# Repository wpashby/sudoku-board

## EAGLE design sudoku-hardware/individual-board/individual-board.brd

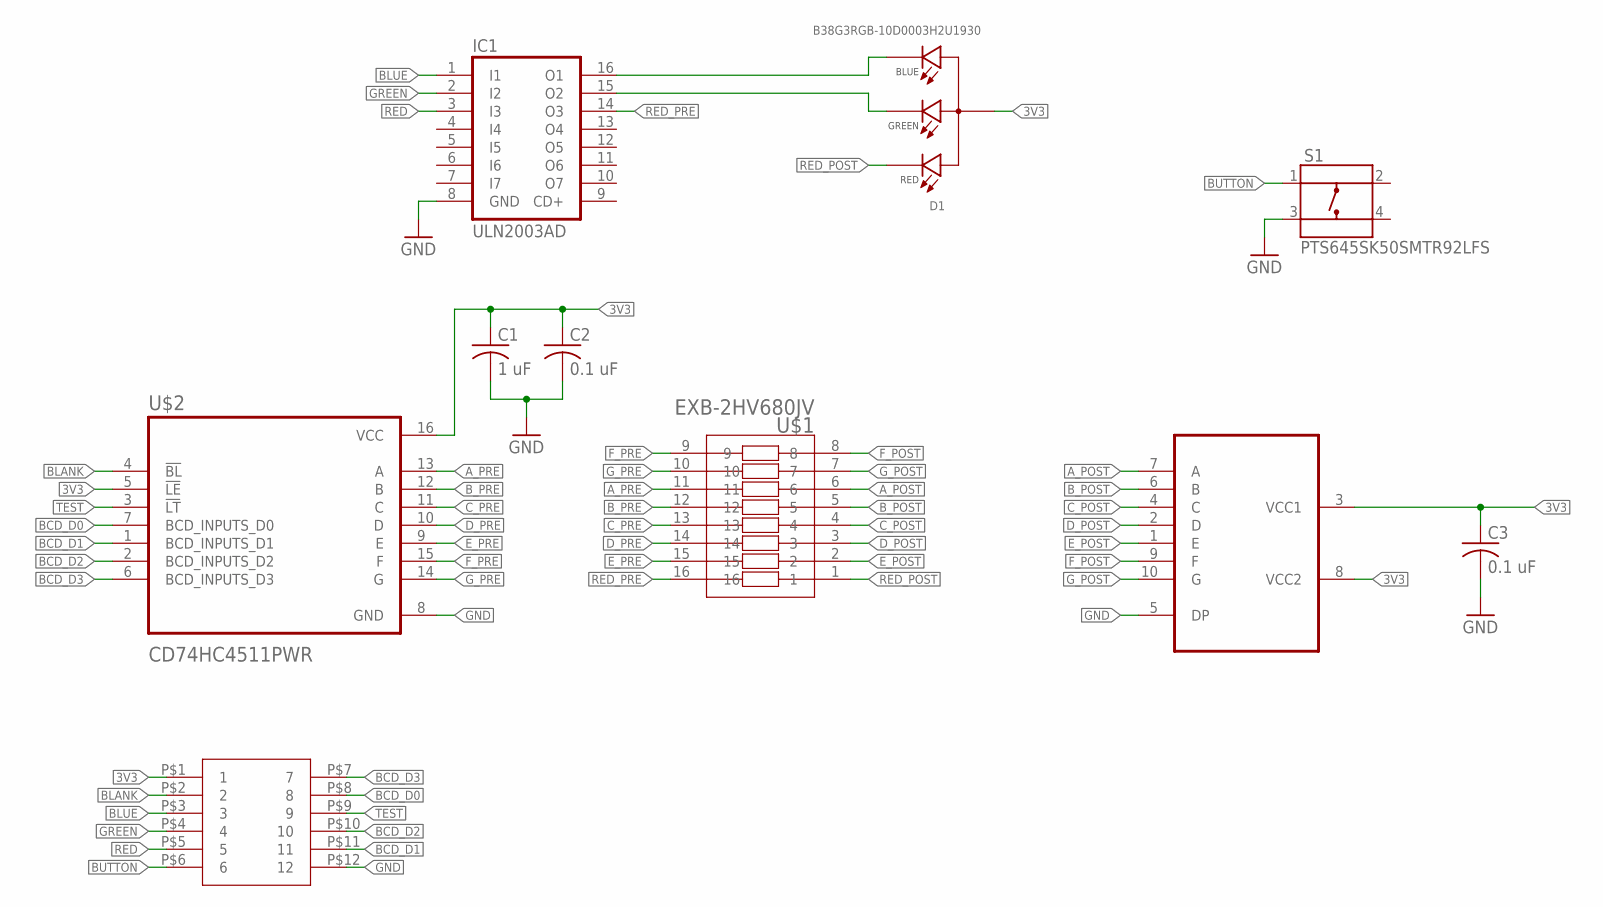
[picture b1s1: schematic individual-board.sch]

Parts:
C1: 1 uF; C0603
C2, C3: 0.1 uF; C0603
D1: B38G3RGB-10D0003H2U1930; LED_B38G3RGB-10D0003H2U1930
IC1: ULN2003AD; SO16
S1: PTS645SK50SMTR92LFS; SW_PTS645SK50SMTR92LFS
U$1: EXB-2HV680JV; 2HV
U$2: CD74HC4511PWR
U$3: INND-SS30RAB
U$4: 2X6-EDGE-CONNECTOR

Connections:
3V3: C1.1, C2.1, C3.1, D1.3 (A), U$2.5 (!LE), U$2.16 (VCC), U$3.3 (VCC1), U$3.8 (VCC2), U$4.P$1 (1)
A_POST: U$1.6, U$3.7 (A)
A_PRE: U$1.11, U$2.13 (A)
BCD_D0: U$2.7 (BCD_INPUTS_D0), U$4.P$8 (8)
BCD_D1: U$2.1 (BCD_INPUTS_D1), U$4.P$11 (11)
BCD_D2: U$2.2 (BCD_INPUTS_D2), U$4.P$10 (10)
BCD_D3: U$2.6 (BCD_INPUTS_D3), U$4.P$7 (7)
BLANK: U$2.4 (!BL), U$4.P$2 (2)
BLUE: IC1.1 (I1), U$4.P$3 (3)
BUTTON: S1.1, U$4.P$6 (6)
B_POST: U$1.5, U$3.6 (B)
B_PRE: U$1.12, U$2.12 (B)
C_POST: U$1.4, U$3.4 (C)
C_PRE: U$1.13, U$2.11 (C)
D_POST: U$1.3, U$3.2 (D)
D_PRE: U$1.14, U$2.10 (D)
E_POST: U$1.2, U$3.1 (E)
E_PRE: U$1.15, U$2.9 (E)
F_POST: U$1.8, U$3.9 (F)
F_PRE: U$1.9, U$2.15 (F)
GND: C1.2, C2.2, C3.2, IC1.8 (GND), S1.3, U$2.8 (GND), U$3.5 (DP), U$4.P$12 (12)
GREEN: IC1.2 (I2), U$4.P$4 (4)
G_POST: U$1.7, U$3.10 (G)
G_PRE: U$1.10, U$2.14 (G)
unnamed: D1.2 (B_C), IC1.16 (O1)
unnamed: D1.1 (G_C), IC1.15 (O2)
RED: IC1.3 (I3), U$4.P$5 (5)
RED_POST: D1.4 (R_C), U$1.1
RED_PRE: IC1.14 (O3), U$1.16
TEST: U$2.3 (!LT), U$4.P$9 (9)

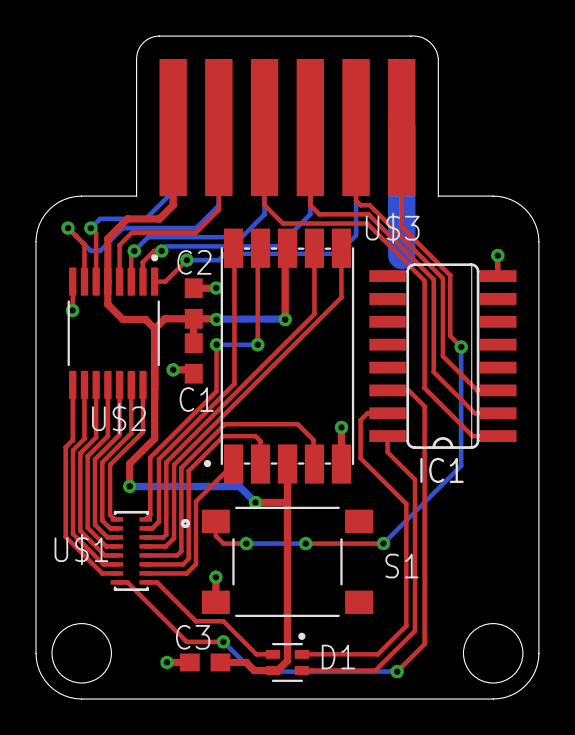
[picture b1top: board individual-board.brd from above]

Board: 2 copper layers, 27.9 x 36.8 mm, 10 parts (0 on the bottom side), 30 nets.

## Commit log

2023-04-19 individual board schematic done, board almost done
2023-04-23 finish individual board, work on debug board
